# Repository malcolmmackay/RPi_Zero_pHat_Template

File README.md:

# RFM69HCW-868-S2 Partial HAT for pi Zero
This project includes KiCAD 5.0 CAD files to make a pi Zero HAT with connections from SPI0 device 0 to an RFM69HCW-868-S2 868 MHz transceiver. It was inspired by the OpenAPS project: https://github.com/openaps/openaps.

This board implements the following connections from the table on https://openaps.readthedocs.io/en/latest/docs/Gear%20Up/edison.html#hardware-information-for-pi-based-setups-with-rfm69hcw-experimental 

| Board | Connect | Connect | Connect | Connect | Connect | Connect | Connect | Connect |
| ----- | ------- | ------- | ------- | ------- | ------- | ------- | ------- | ------- |
| RPi | 3.3V | GND | MOSI | MISO | SCLK | | CEO_N | | 
| RPi PIN | 17 | 25 | 19 | 21 | 23 | 16 | 24 | 18 |
| RFM69HCW | VIN or 3.3V | GND | MOSI | MISO | SCK or CLK | G0 or DIO0 | CS or NSS | RST or RESET |

One of five prototypes made by Eurocircuits for £42 was tested successfully with OpenAPS after following instructions to switch to the development branch.

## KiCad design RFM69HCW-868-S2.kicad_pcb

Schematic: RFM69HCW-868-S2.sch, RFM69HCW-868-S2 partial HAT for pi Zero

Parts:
AE1: 0868AT43A0020E
C1: 3P9; C_0603
C2: 0P3; C_0603
C3: 100N; C_0603
C4: 1U; C_0603
J2: RPi_GPIO; PinHeader_2x20_P2.54mm_Vertical
L1: 18N; R_0402
U1: RFM69HCW; RFM69HCW-XXXS2

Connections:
+3V3: C3.1, C4.1, J2.17, U1.13 (3.3V)
GND: C1.2, C2.2, C3.2, C4.2, J2.6, J2.9, J2.14, J2.25, J2.39, U1.1 (GND), U1.8 (GND), U1.10 (GND)
unnamed: AE1.2, C2.1, L1.2
unnamed: C1.1, L1.1, U1.9 (ANT)
unnamed: J2.16, U1.14 (DIO0)
unnamed: J2.18, U1.6 (RESET)
unnamed: J2.19, U1.3 (MOSI)
unnamed: J2.21, U1.2 (MISO)
unnamed: J2.23, U1.4 (SCK)
unnamed: J2.24, U1.5 (NSS)

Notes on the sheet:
Thru-Hole Connector

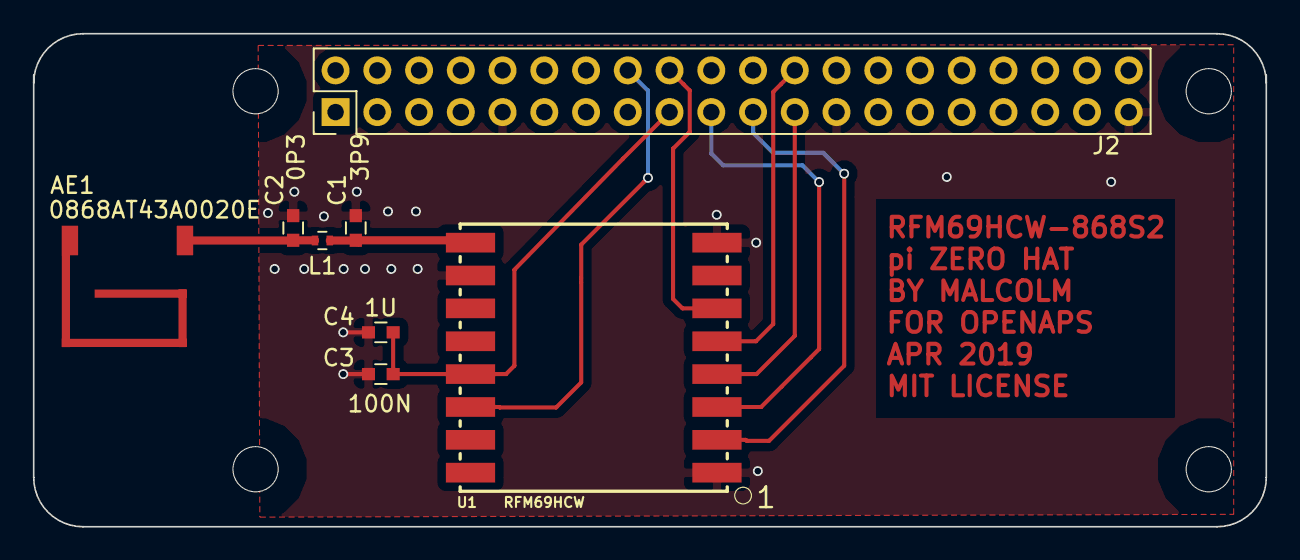
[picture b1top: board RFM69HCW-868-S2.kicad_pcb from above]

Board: 2 copper layers, 75.0 x 30.0 mm, 8 parts (0 on the bottom side), 10 nets.

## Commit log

2019-04-29 PCB sent out for manufacture.
2019-04-29 Added Gerber files and improved documentation
2019-04-29 Renamed files to match project name
    Improved documentation
2019-04-29 Update LICENSE
2019-04-29 Auto stash before merge of "RFM69HCW-868-S2" and "origin/RFM69HCW-868-S2"
    Added a photo
2019-04-29 Added photo to readme
2019-04-29 Less wordy.

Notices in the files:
RFM69HCW-868-S2.kicad_pcb:
MIT Licensed Open Source Hardware
MIT LICENSE
